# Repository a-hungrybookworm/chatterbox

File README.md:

# The Chatterbox

The Chatterbox is a tiny motion-controlled, talkative digital pet, basically a desktop Tamagotchi, or a Starbie that talks.

# Features
- Tilt-controlled radial menu
- Tiny virtual pet on-screen
- Motion, tilt and environment sensing
- Unique pet actions, stats, dialogues
- Compact PCB design

# Why it was built
The Chatterbox was built for the Hack Club YSWS Programme [Halflife](https://halflife.hackclub.com/), drawing inspiration from the project [Starbie](https://github.com/SharKingStudios/Starbie/blob/main/README.md). 

# Components
This project was built using the following components:
* XIAO-ESP32-C3
* 1W Speaker
* MAX98357A amplifier
* DHT11 temperature and humidity sensor
* MPU6050 accelerometer and gyroscope
* 0.96 OLED screen
* Kailh switches
* DSA keycaps

# Building it!
Following the Starbie tutorial, the PCB schematic for this project was initially created on KiCAD. After verifying all connections, the components were assigned footprints, and placed on the PCB. They were compactly arranged inside a custom outer boundary and routed along with ground fills. 

The firmware is nearly identical to that of the Starbie. The tiny virtual pet on the OLED has different energy, joy, and fullness levels, and reacts to stimuli (tilting, shaking) by performing different reactions such as napping, running, jumping etc. 

However, to enable the Chatterbox to speak (unlike the Starbie), I had to write code to convert voice recordings (.wav's) to playable audio on the Chatterbox speaker. The .wav recordings are first processed into mono 16kHz audio, and then converted to C++ header files. They're compiled into the firmware, stored in the ESP32's flash on uploading, and a background FreeRTOS task streams the audio to an amplifier at runtime, which plays it on a speaker without interrupting the pet's animations.

# What I learnt
This was one of the first hardware projects I've done, and I learnt a lot, including how to - 
- add power symbols and nets in KiCAD
- fill ground areas in KiCAD
- process wav audio
- create tasks and queues on FreeRTOS (on the ESP32)

# BOM

| Part | What it's for | Qty | Unit | Total | Vendor |
| --- | --- | --- | --- | --- | --- |
| [XIAO-ESP32-C3](https://robu.in/product/seeed-studio-xiao-esp32c3-tiny-mcu-board-with-wi-fi-and-ble-battery-charge-supported-power-efficiency-and-rich-interface/) | Microcontroller | 1 | $7.74 | $7.74 | [Robu.in](https://robu.in/product/seeed-studio-xiao-esp32c3-tiny-mcu-board-with-wi-fi-and-ble-battery-charge-supported-power-efficiency-and-rich-interface/) |
| [MAX98357A Amplifier](https://robu.in/product/smartelex-i2s-audio-breakout-max98357a/) | Amp for the speaker | 1 | $2.00 | $2.00 | [Robu.in](https://robu.in/product/smartelex-i2s-audio-breakout-max98357a/) |
| [DHT11](https://robocraze.com/products/dht11-humidity-temperature-sensor-module-1) | Environment sensor | 1 | $0.53 | $0.53 | [Robocraze.com](https://robocraze.com/products/dht11-humidity-temperature-sensor-module-1) |
| [MPU6050](https://robocraze.com/products/mpu-6050-triple-axis-accelerometer-gyroscope-module) | Accelerometer & gyroscope | 1 | $1.56 | $1.56 | [Robocraze.com](https://robocraze.com/products/mpu-6050-triple-axis-accelerometer-gyroscope-module) |
| [0.96 OLED](https://robocraze.com/products/0-96in-oled-display-module-4pin) | Display | 1 | $1.75 | $1.75 | [Robocraze.com](https://robocraze.com/products/0-96in-oled-display-module-4pin) |
| [Kailh Switches (pack of 10)](https://meckeys.com/shop/accessories/keyboard-accessories/key-switches/kailh-switch-pack/) | Controls (buttons) | 1 | $1.45 | $1.45 | [Meckeys.com](https://meckeys.com/shop/accessories/keyboard-accessories/key-switches/kailh-switch-pack/) |
| [Blank DSA Keycaps (Set of 5)](https://meckeys.com/shop/accessories/keyboard-accessories/keycaps/blank/blank-dsa-keycaps-1u/) | Keycaps for the buttons | 1 | $1.03 | $1.03 | [Meckeys.com](https://meckeys.com/shop/accessories/keyboard-accessories/keycaps/blank/blank-dsa-keycaps-1u/) |
| [Speaker (1 Watt 8 Ohm oval mini)](https://probots.co.in/8-ohm-1w-1510-mm-oval-mini-audio-speaker.html) | Talking! | 1 | $0.51 | $0.51 | [Probots](https://probots.co.in/8-ohm-1w-1510-mm-oval-mini-audio-speaker.html) |
| [PCB](https://robu.in/product/online-pcb-manufacturing-service/) | Circuitry & connections | 1 | $9.30 | $9.30 | [Robu.in](https://robu.in/product/online-pcb-manufacturing-service/) |
| **Parts subtotal** | — | — | — | **$25.87** | — |
| **Tax & shipping** | — | — | — | **$3.06** | — |
| **Total** | — | — | — | **$28.93** | — |

# Images and Renders
The final schematic looks like this:

And this is the final PCB:

A 3D render of the PCB:

# Credits
This project would not have been possible without the constant support of the Halflife community, and the detailed guidance given in the Starbie guide. I loved designing this project and I can't wait to build the PCB!

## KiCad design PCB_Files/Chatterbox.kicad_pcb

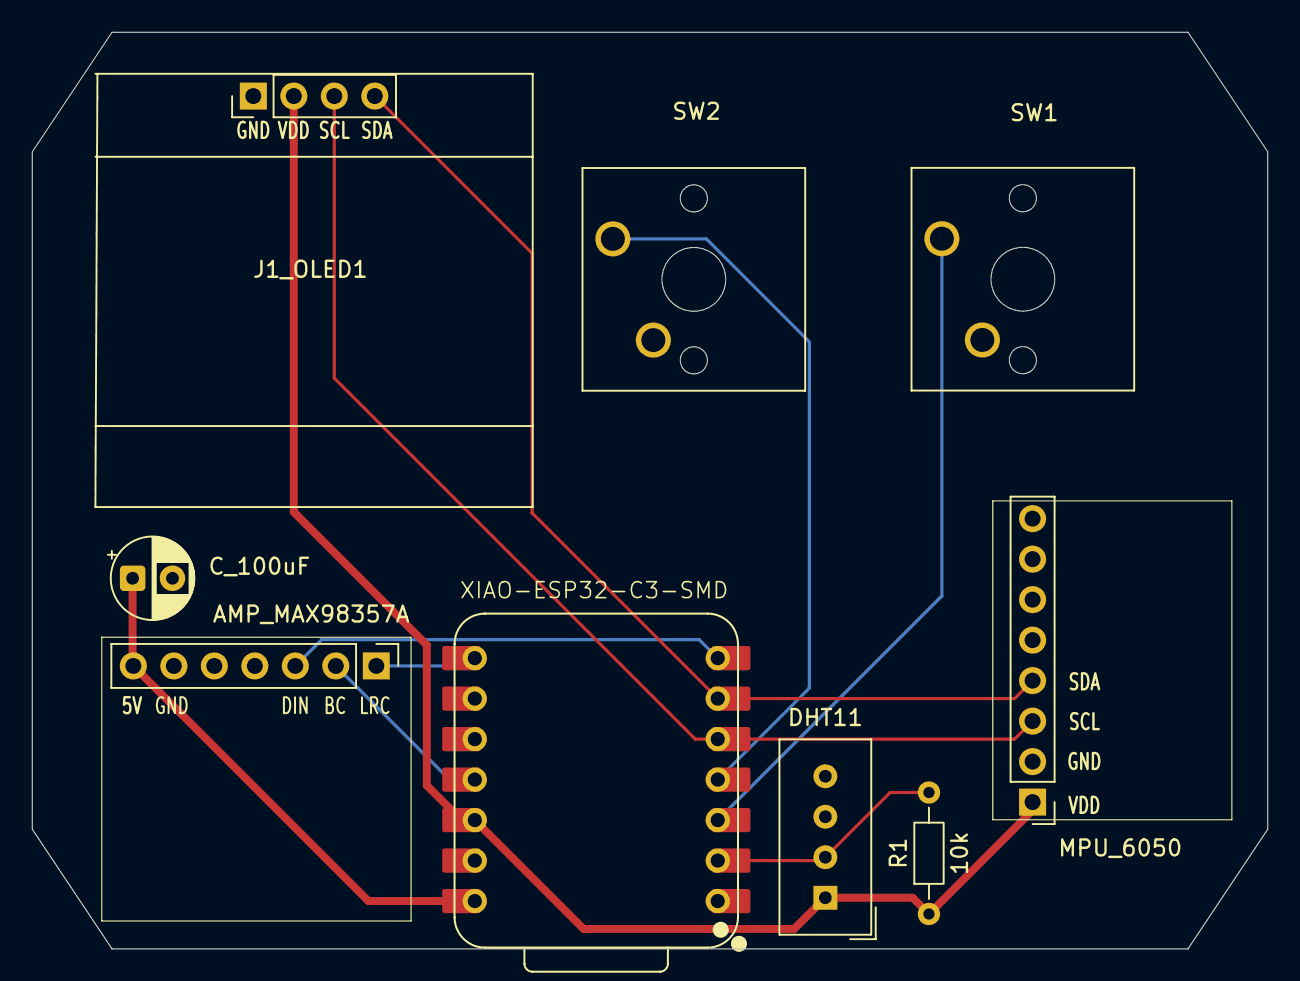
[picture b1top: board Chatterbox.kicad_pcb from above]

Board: 2 copper layers, 77.5 x 57.5 mm, 9 parts (0 on the bottom side), 11 nets.

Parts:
AMP_MAX98357A: AMP; PinHeader_1x07_P2.54mm_Vertical
C1: C_100uF; CP_Radial_D5.0mm_P2.50mm
J1_OLED1: Conn_01x04_Pin; Display_128x64_096_I2C
MPU_6050: Conn_01x08_Pin; PinHeader_1x08_P2.54mm_Vertical
R1: 10k; R_Axial_DIN0204_L3.6mm_D1.6mm_P7.62mm_Horizontal
SW1, SW2: SW_Push; SW_Cherry_MX_1.00u_PCB
U1: DHT11; Aosong_DHT11_5.5x12.0_P2.54mm
U2: XIAO-ESP32-C3-SMD; XIAO-ESP32-C6-DIP

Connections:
+3.3V: J1_OLED1.2, MPU_6050.1, R1.1, U1.1 (VDD), U2.12 (3V3_OUT)
+5V: AMP_MAX98357A.7, C1.1, U2.14 (VBUS)
/AMP BCLK: AMP_MAX98357A.2, U2.11 (D10)
/AMP DIN: AMP_MAX98357A.3, U2.7 (D6)
/AMP LRC: AMP_MAX98357A.1, U2.8 (D7)
/DHT11 DATA: R1.2, U1.2 (DATA), U2.2 (D1)
/GPIO2: SW1.1, U2.3 (D2)
/GPIO3: SW2.1, U2.4 (D3)
/SCL: J1_OLED1.3, MPU_6050.3, U2.5 (D4)
/SDA: J1_OLED1.4, MPU_6050.4, U2.6 (D5)
GND: AMP_MAX98357A.6, C1.2, J1_OLED1.1, MPU_6050.2, SW1.2, SW2.2, U1.4 (GND), U2.13 (GND)
